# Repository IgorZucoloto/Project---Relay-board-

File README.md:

# Módulo Relé 5V

Projeto de placa PCB para acionamento de relé utilizando transistor NPN.

## 📌 Especificações

- Tensão de acionamento: 5V
- Relé: SRD-05VDC-SL-C
- Transistor driver
- Diodo de flyback para proteção

## 📷 Render 3D

## 📂 Arquivos do projeto

- Esquemático (Placa 1 - Módulo Relé.kicad_sch)
- PCB (Placa 1 - Módulo Relé.kicad_pcb)
- Arquivo do projeto (Placa 1 - Módulo Relé.kicad_pro)

## 🛠️ Software

Desenvolvido no KiCad.

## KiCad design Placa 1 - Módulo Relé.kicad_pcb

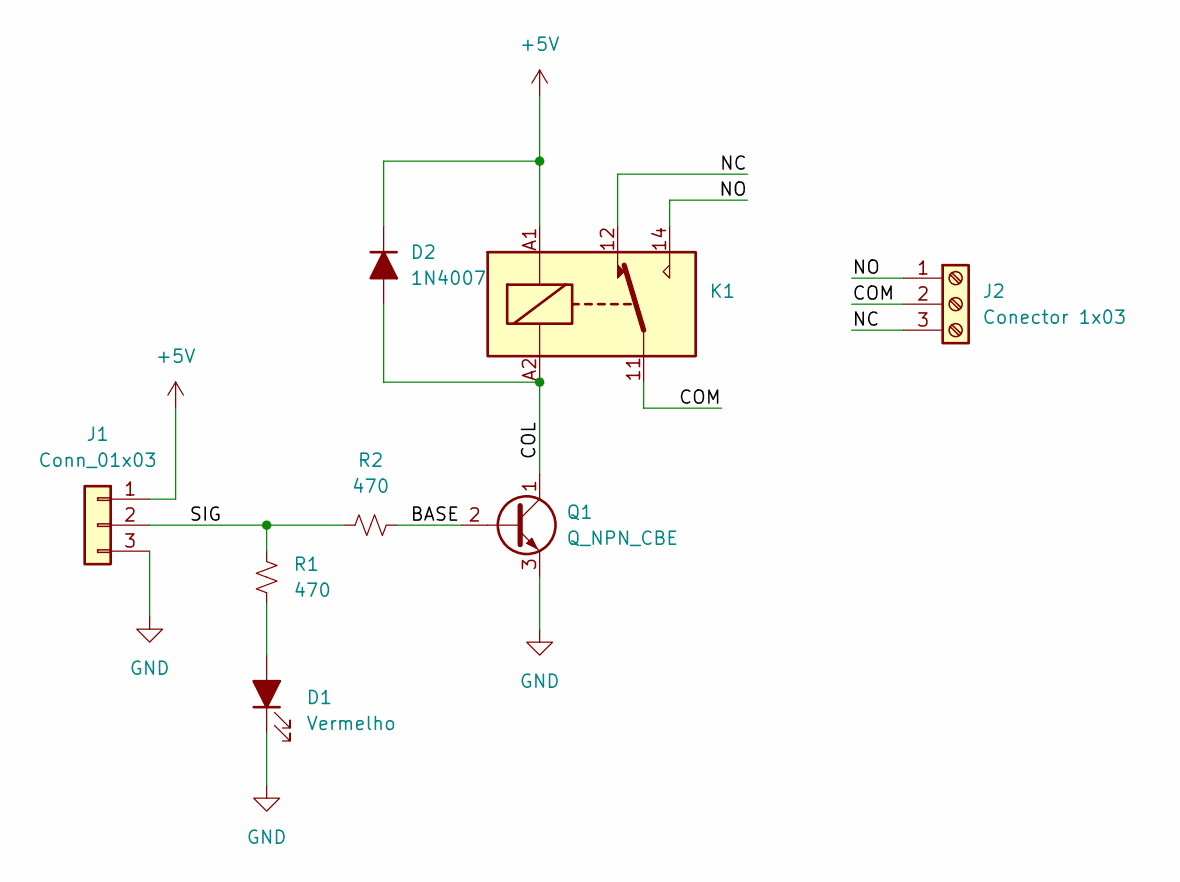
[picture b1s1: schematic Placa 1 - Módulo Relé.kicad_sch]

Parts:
D1: Vermelho; LED_D5.0mm
D2: 1N4007; D_DO-41_SOD81_P10.16mm_Horizontal
J1: Conn_01x03; PinHeader_1x03_P2.54mm_Vertical
J2: Conector 1x03; TerminalBlock_Phoenix_MKDS-1,5-3-5.08_1x03_P5.08mm_Horizont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
K1: Relay_SPDT; Relay_SPDT_Finder_36.11
Q1: Q_NPN_CBE; TO-92L_Inline_Wide
R1, R2: 470; R_Axial_DIN0207_L6.3mm_D2.5mm_P10.16mm_Horizontal

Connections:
+5V: D2.1 (K), J1.1, K1.A1
/BASE: Q1.2 (B), R2.2
/COL: D2.2 (A), K1.A2, Q1.1 (C)
/COM: J2.2, K1.11
/NC: J2.3, K1.12
/NO: J2.1, K1.14
/SIG: J1.2, R1.1, R2.1
GND: D1.1 (K), J1.3, Q1.3 (E)
unnamed: D1.2 (A), R1.2

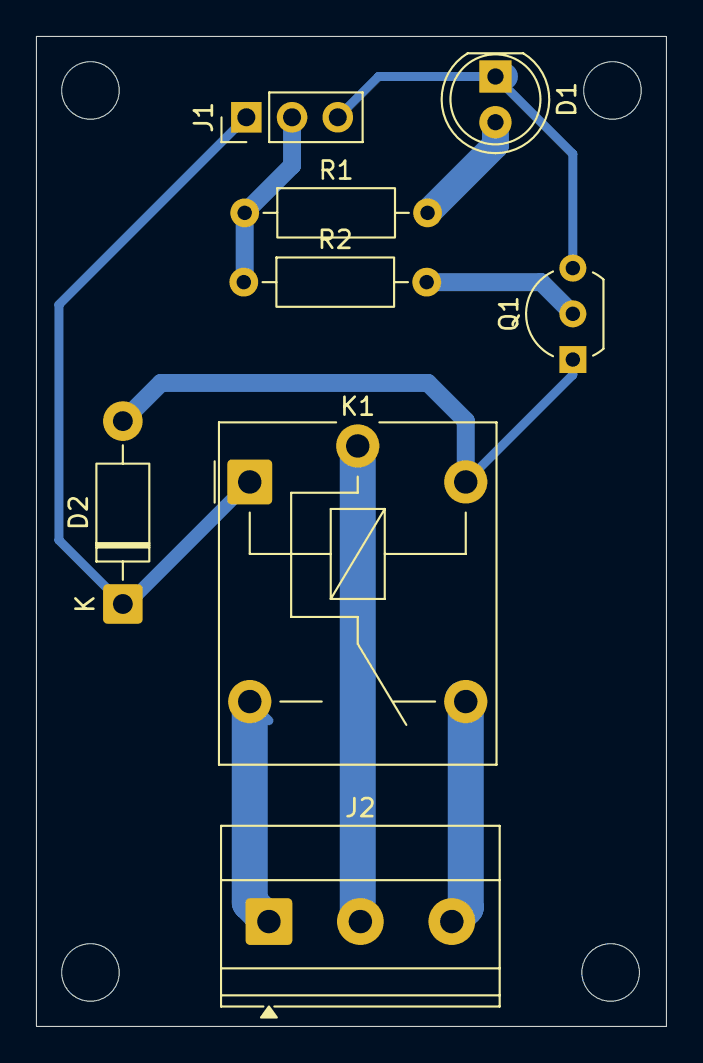
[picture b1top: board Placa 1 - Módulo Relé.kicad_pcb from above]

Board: 2 copper layers, 35.0 x 55.0 mm, 8 parts (0 on the bottom side), 9 nets.

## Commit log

2026-02-14 Primeira Versão
2026-02-14 render.png
